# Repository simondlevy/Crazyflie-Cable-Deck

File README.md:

# Crazyflie-Cable-Deck
A Crazyflie expansion deck with JST SH 1.0 cable connectors

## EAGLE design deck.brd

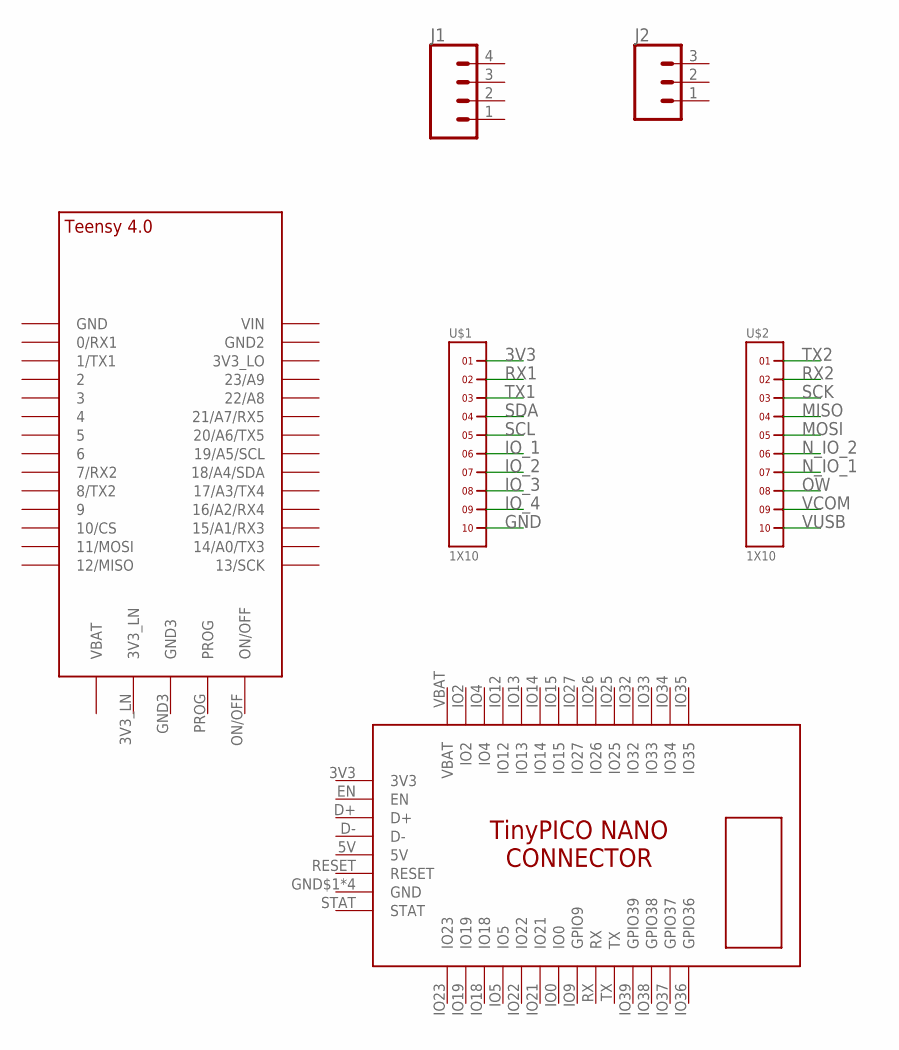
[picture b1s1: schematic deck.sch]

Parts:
J1: CONN_041X04_NO_SILK; 1X04_NO_SILK
J2: CONN_031X03_NO_SILK; 1X03_NO_SILK
U$1, U$2: 1X10
U$3: TEENSY_4.0
U$4: TINYPICO-NANO-CONNECTOR

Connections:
3V3: U$1.1, U$4.3V3
5V: U$4.5V
GND: U$1.10, U$4.GND$1 (GND), U$4.GND$2 (GND), U$4.GND$3 (GND), U$4.GND$4 (GND)
IO_1: U$1.6
IO_2: U$1.7
IO_3: U$1.8
IO_4: U$1.9
MISO: U$2.4
MOSI: U$2.5
N_IO_1: U$2.7
N_IO_2: U$2.6
OW: U$2.8
RX1: U$1.2
RX2: U$2.2
SCK: U$2.3
SCL: U$1.5
SDA: U$1.4
TX1: U$1.3
TX2: U$2.1
VBAT: U$4.VBAT
VCOM: U$2.9
VUSB: U$2.10

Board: 2 copper layers, 6 parts (0 on the bottom side), 2 nets, no tracks yet.

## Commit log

2023-07-30 Finished 10-pin JST SH1
2023-07-30 More board design

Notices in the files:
parts and their libraries:
SparkFun-Connectors: Licensing: Creative Commons ShareAlike 4.0 International - https://creativecommons.org/licenses/by-sa/4.0
